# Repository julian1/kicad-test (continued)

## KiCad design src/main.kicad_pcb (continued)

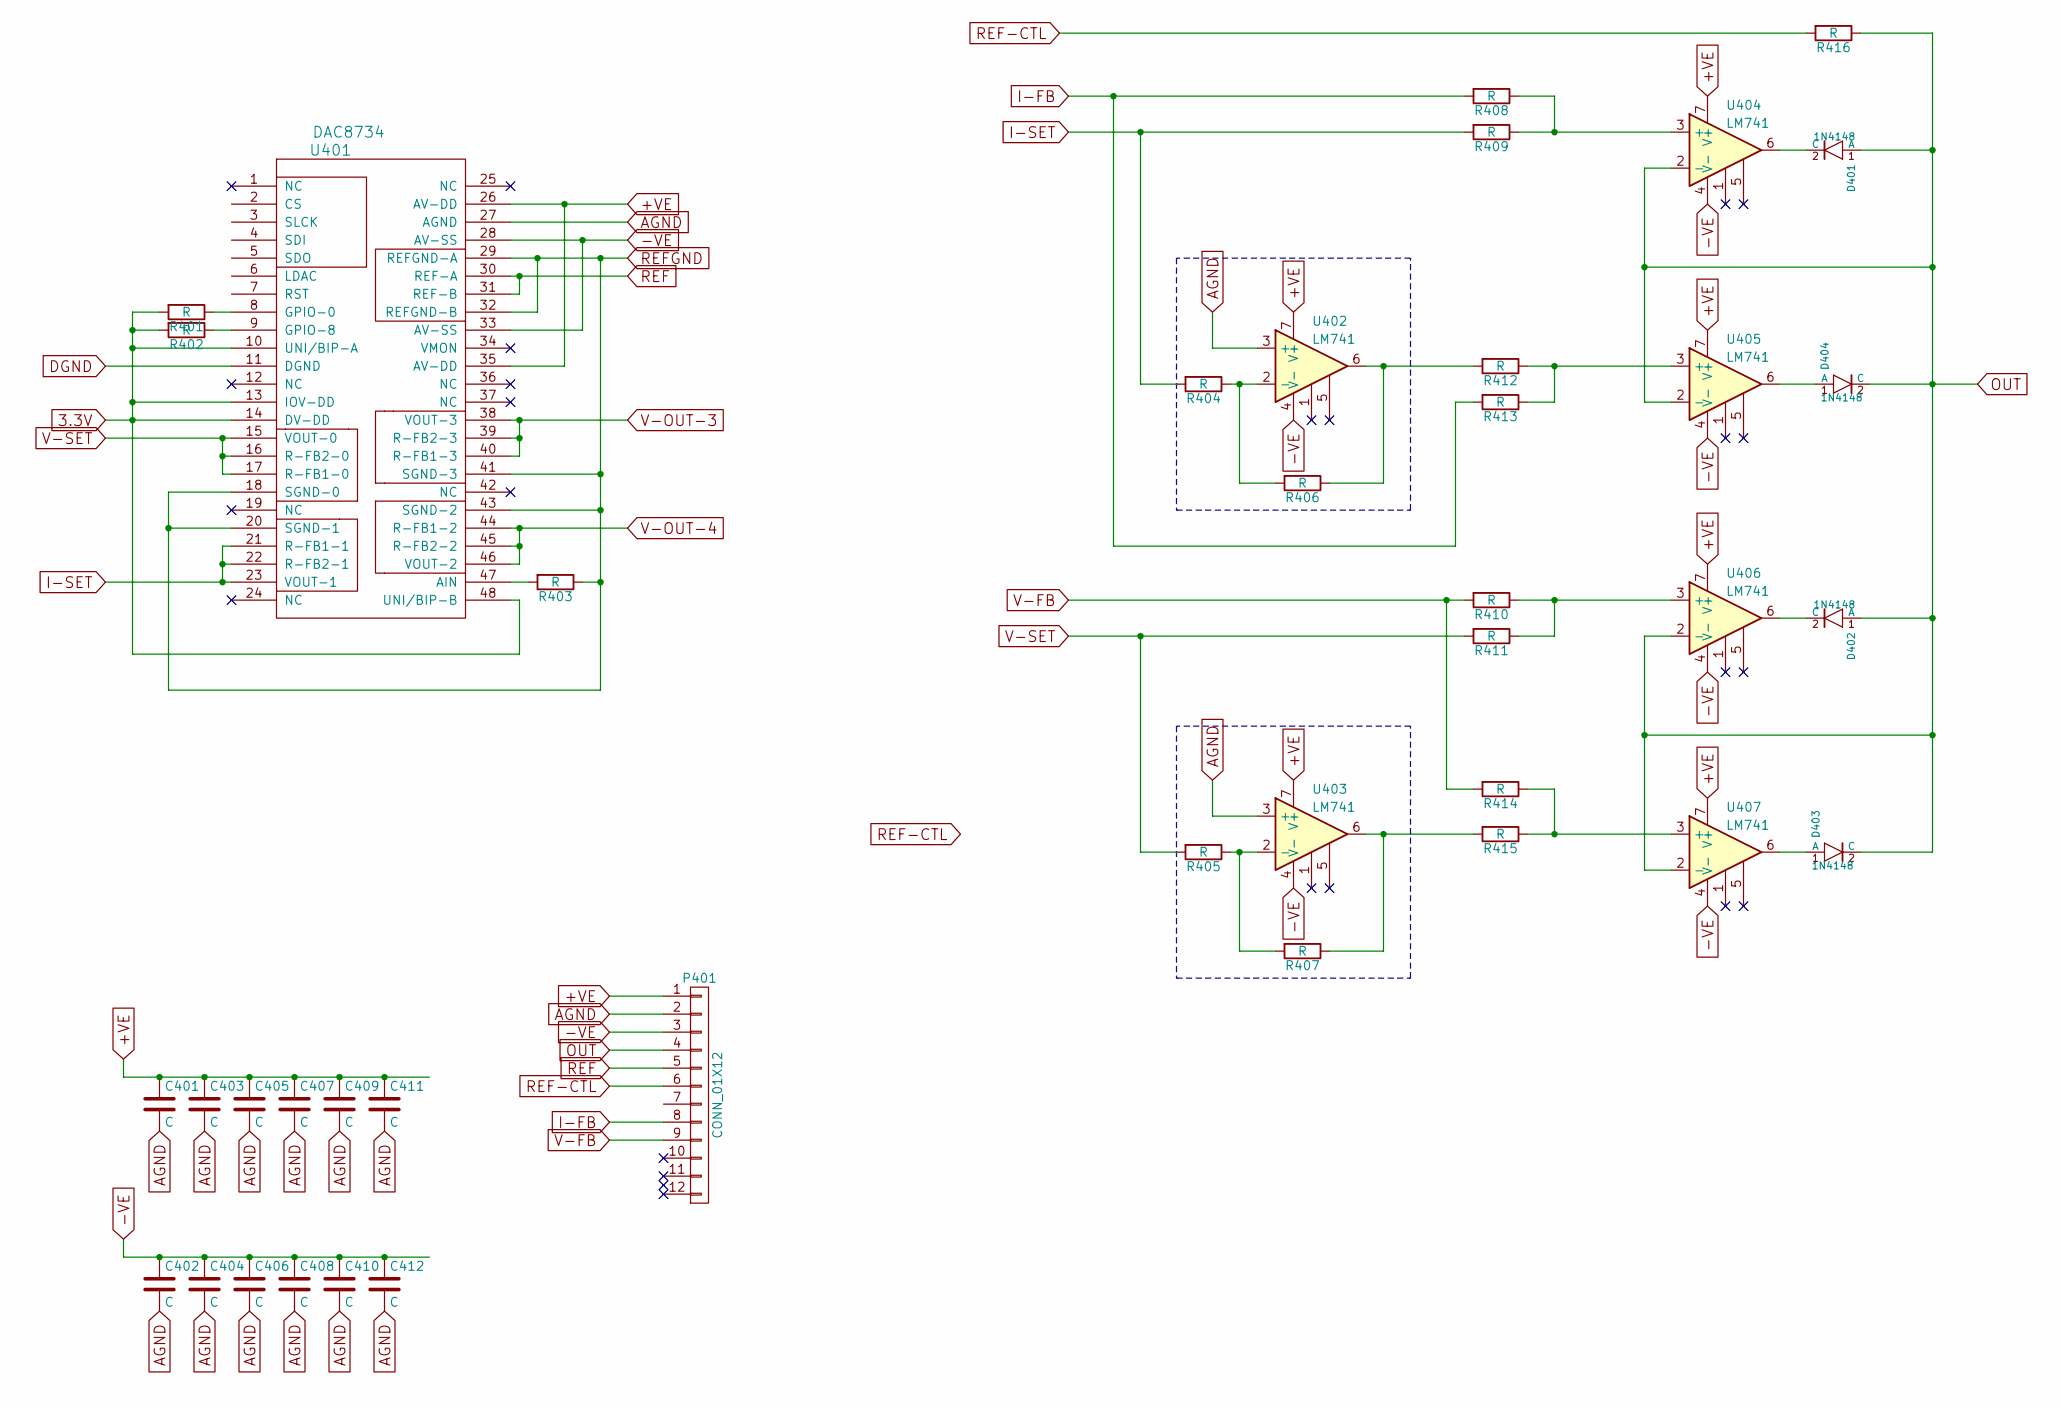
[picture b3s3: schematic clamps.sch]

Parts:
C401, C402, C403, C404, C405, C406, C407, C408, C409, C410, C411, C412: C; C_1206
D401, D402, D403, D404: 1N4148; MiniMELF_Standard
P401: CONN_01X12; Pin_Header_Straight_1x12
R401, R402, R403: R
R404, R405, R406, R407, R408, R409, R410, R411, R412, R413, R414, R415, R416: R; R_1206
U401: DAC8734
U402, U403, U404, U405, U406, U407: LM741; SOIC-8_3.9x4.9mm_Pitch1.27mm

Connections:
3.3V: R401.2, R402.2, U401.10 (UNI/BIP-A), U401.13 (IOV-DD), U401.14 (DV-DD), U401.48 (UNI/BIP-B); also elsewhere on the board
+VE: C401.1, C403.1, C405.1, C407.1, C409.1, C411.1, P401.1, U401.26 (AV-DD), U401.35 (AV-DD), U402.7 (V+), U403.7 (V+), U404.7 (V+), U405.7 (V+), U406.7 (V+), U407.7 (V+); also elsewhere on the board
-VE: C402.1, C404.1, C406.1, C408.1, C410.1, C412.1, P401.3, U401.28 (AV-SS), U401.33 (AV-SS), U402.4 (V-), U403.4 (V-), U404.4 (V-), U405.4 (V-), U406.4 (V-), U407.4 (V-); also elsewhere on the board
I-FB: P401.8, R408.2, R413.2
I-SET: R404.2, R409.2, U401.21 (R-FB1-1), U401.22 (R-FB2-1), U401.23 (VOUT-1)
unnamed: D401.2 (C), U404.6
unnamed: D402.2 (C), U406.6
unnamed: D403.1 (A), U407.6
unnamed: D404.1 (A), U405.6
unnamed: R401.1, U401.8 (GPIO-0)
unnamed: R402.1, U401.9 (GPIO-8)
unnamed: R403.2, U401.47 (AIN)
unnamed: R404.1, R406.2, U402.2 (-)
unnamed: R405.1, R407.2, U403.2 (-)
unnamed: R406.1, R412.2, U402.6
unnamed: R407.1, R415.2, U403.6
unnamed: R408.1, R409.1, U404.3 (+)
unnamed: R410.1, R411.1, U406.3 (+)
unnamed: R412.1, R413.1, U405.3 (+)
unnamed: R414.1, R415.1, U407.3 (+)
OUT: D401.1 (A), D402.1 (A), D403.2 (C), D404.2 (C), P401.4, R416.1, U404.2 (-), U405.2 (-), U406.2 (-), U407.2 (-)
REF: P401.5, U401.30 (REF-A), U401.31 (REF-B); also elsewhere on the board
REF-CTL: P401.6, R416.2
REFGND: R403.1, U401.18 (SGND-0), U401.20 (SGND-1), U401.29 (REFGND-A), U401.32 (REFGND-B), U401.41 (SGND-3), U401.43 (SGND-2)
V-FB: P401.9, R410.2, R414.2
V-OUT-3: U401.38 (VOUT-3), U401.39 (R-FB2-3), U401.40 (R-FB1-3)
V-OUT-4: U401.44 (R-FB1-2), U401.45 (R-FB2-2), U401.46 (VOUT-2)
V-SET: R405.2, R411.2, U401.15 (VOUT-0), U401.16 (R-FB2-0), U401.17 (R-FB1-0)

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
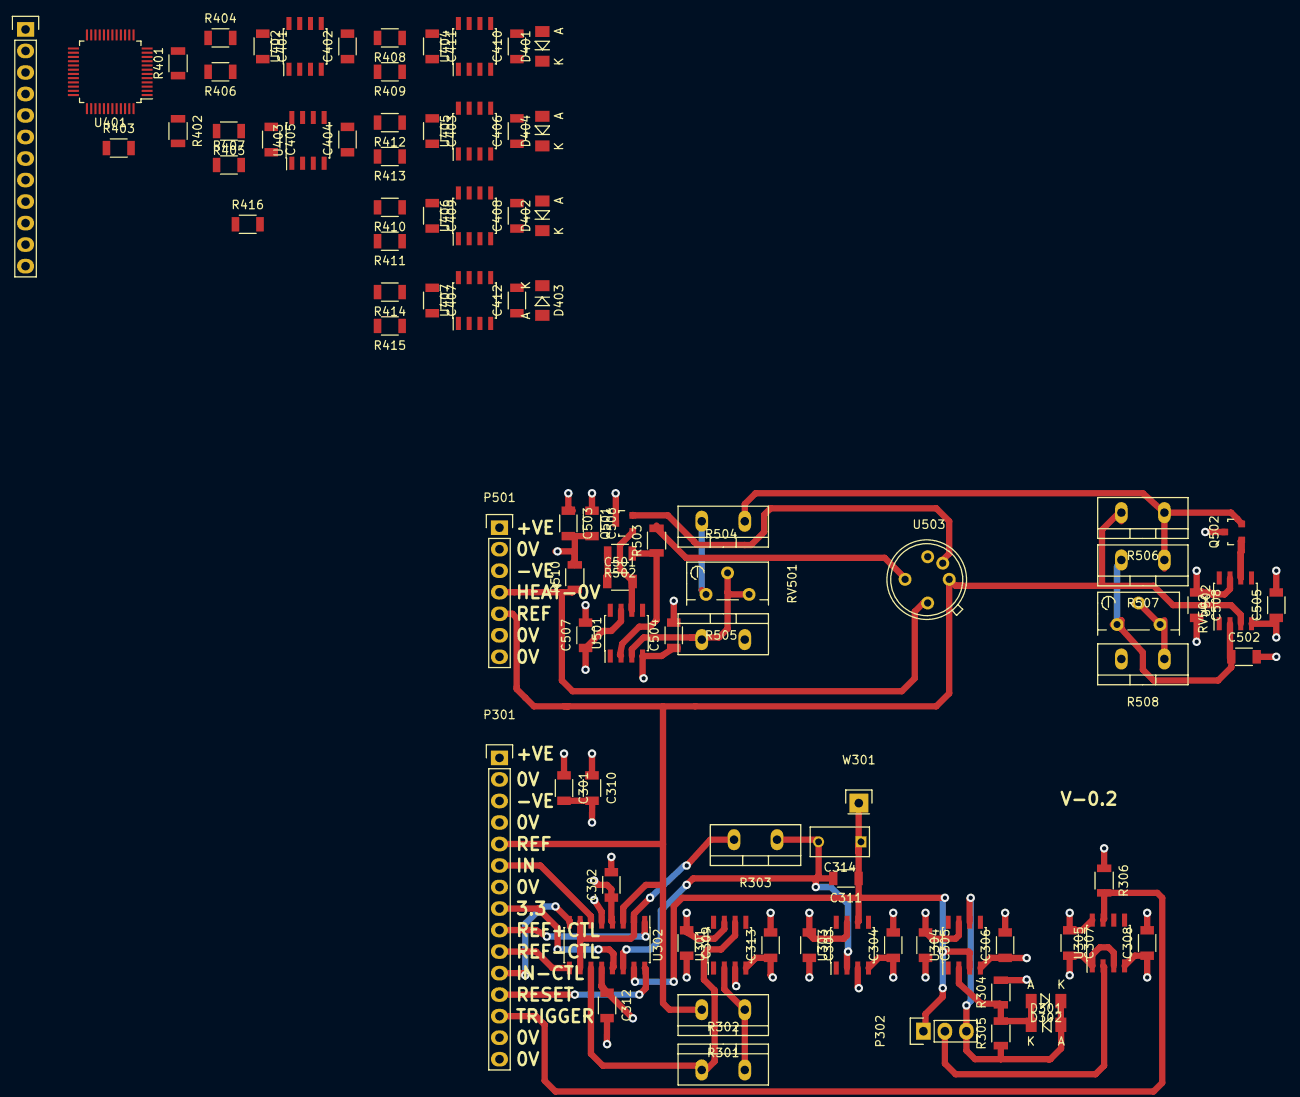
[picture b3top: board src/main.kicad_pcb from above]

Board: 4 copper layers, 94 parts (0 on the bottom side), 55 nets.

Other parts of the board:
R303: R; Resistor_TO-220_Vertical
U302: DG444; SOIC-16_3.9x9.9mm_Pitch1.27mm
U303: LM741; SOIC-8_3.9x4.9mm_Pitch1.27mm

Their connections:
3.3V: U302.13; also elsewhere on the board
+VE: U302.12, U303.7; also elsewhere on the board
-VE: U302.4, U303.4; also elsewhere on the board
IN: U302.6; also elsewhere on the board
IN_CTL: U302.8; also elsewhere on the board
unnamed 8: U302.15, U303.6; also elsewhere on the board
unnamed 9: R303.1, U302.14, U303.2; also elsewhere on the board
unnamed 24: U302.11; also elsewhere on the board
unnamed: R303.2, U302.2, U302.7, U302.10
REF: U302.3; also elsewhere on the board
REF_PLUS_CTL: U302.1; also elsewhere on the board
REF_SUB_CTL: U302.9; also elsewhere on the board
RESET: U302.16; also elsewhere on the board

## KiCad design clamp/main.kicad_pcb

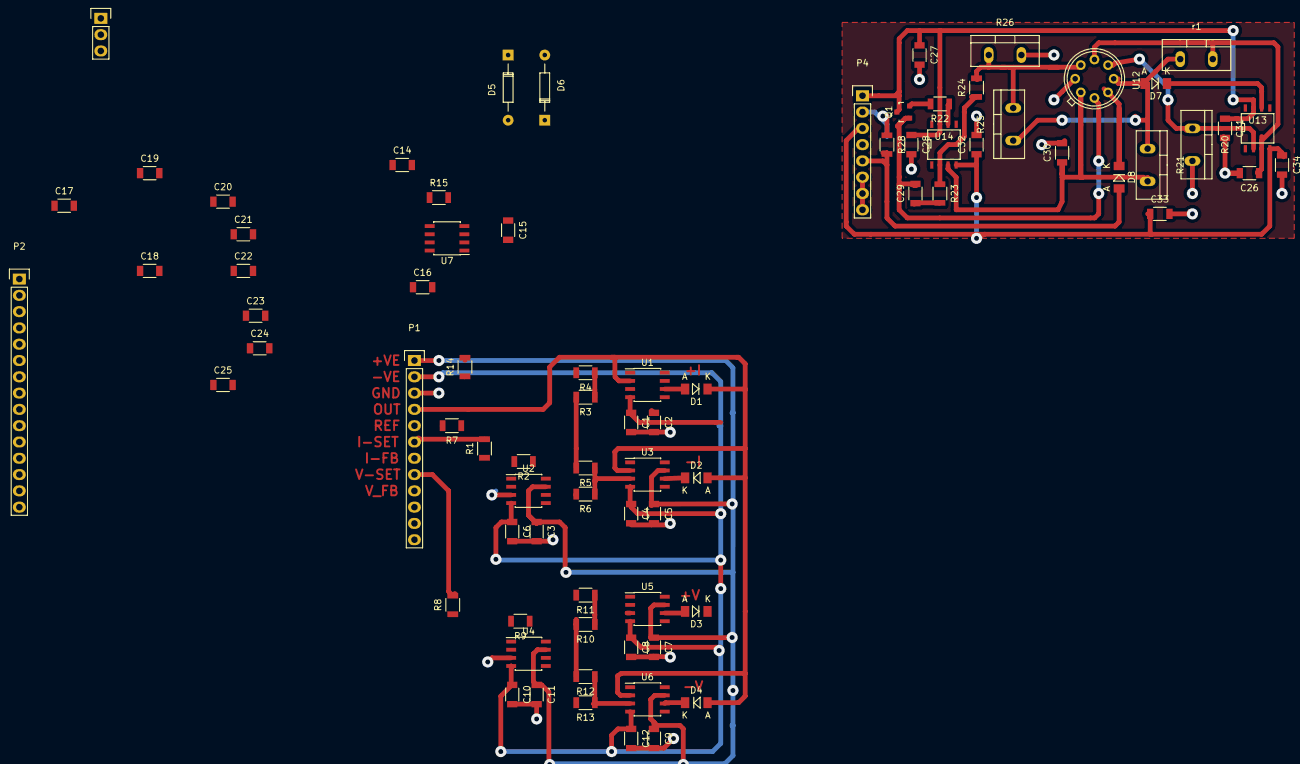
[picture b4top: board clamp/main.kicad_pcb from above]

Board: 2 copper layers, 80 parts (0 on the bottom side), 37 nets.

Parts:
C1, C2, C3, C4, C5, C6, C7, C8, C9, C10, C11, C12, C14, C15, C16, C17, C18, C19, C20, C21, C22, C23, C24, C25: C; C_1206
C26: 22nF; C_1206
C27, C33: 10uF; C_1206
C28, C29, C30, C31, C32, C34: 0.1uF; C_1206
D1, D2, D3, D4, D7, D8: 1N4148; MiniMELF_Standard
D5, D6: 1N4148; Diode_DO-35_SOD27_Horizontal_RM10
P1: CONN_01X12; Pin_Header_Straight_1x12
P2: CONN_01X15; Pin_Header_Straight_1x15
P3: CONN_01X03; Pin_Header_Straight_1x03
P4: CONN_01X08; Pin_Header_Straight_1x08
Q1: 2N3904; SOT-23
R1, R2, R3, R4, R5, R6, R7, R8, R9, R10, R11, R12, R13, R14, R15: R; R_1206
R20: 120; Resistor_TO-220_Vertical
R21: 70k; Resistor_TO-220_Vertical
R22: 1k; R_1206
R23: 1M; R_1206
R24: 10k; R_1206
R25: 12k; Resistor_TO-220_Vertical
R26: 1k; Resistor_TO-220_Vertical
R28: 0; R_1206
U1, U2, U3, U4, U5, U6, U7: LM741; SOIC-8_3.9x4.9mm_Pitch1.27mm
U12: LTZ1000; TO-5_Housing_8Pin
U13, U14: LM741; SOIC-8-N
r1: 70k; Resistor_TO-220_Vertical

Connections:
+VE: C1.1, C3.1, C5.1, C7.1, C9.1, C11.1, C14.1, C16.1, C18.1, C20.1, C22.1, C24.1, C27.1, C28.1, C31.1, P1.1, P2.1, P4.1, Q1.3, U1.7, U2.7, U3.7, U4.7, U5.7, U6.7, U7.7, U13.7, U14.7
-VE: C2.1, C4.1, C6.1, C8.1, C10.1, C12.1, C15.1, C17.1, C19.1, C21.1, C23.1, C25.1, C32.1, C33.1, C34.1, P1.2, P2.3, P4.3, U1.4, U2.4, U3.4, U4.4, U5.4, U6.4, U7.4, U13.4, U14.4
GND: C1.2, C2.2, C3.2, C4.2, C5.2, C6.2, C7.2, C8.2, C9.2, C10.2, C11.2, C12.2, C14.2, C15.2, C16.2, C17.2, C18.2, C19.2, C20.2, C21.2, C22.2, C23.2, C24.2, C25.2, C26.2, C27.2, C28.2, C30.2, C31.2, C32.2, C33.2, C34.2, P1.3, P2.2, P2.4, P2.7, P2.14, P2.15, P4.2, P4.6, P4.7, P4.8, R20.2, R26.2, R28.1, U1.3, U2.3, U7.3, U12.7
GND-H: D8.2, P4.5, R28.2
I-FB: P1.7, R5.2, R10.2
I-SET: P1.6, R1.2, R6.2
unnamed: C26.1, U12.5, U13.3, r1.2
unnamed: C29.1, R23.2
unnamed: C29.2, Q1.1, U12.1
unnamed: C30.1, R21.2, U12.8, U14.3
unnamed: D1.2, U3.6
unnamed: D2.2, U5.6
unnamed: D3.1, U6.6
unnamed: D4.1, U4.6
unnamed: D5.1, D6.2
unnamed: D5.2, D6.1, P3.3
unnamed: D7.1, U13.6
unnamed: D8.1, U12.2
unnamed: Q1.2, R22.2
unnamed: R1.1, R3.2, U1.2
unnamed: R2.1, R4.2, U2.2
unnamed: R3.1, R9.2, U1.6
unnamed: R5.1, R6.1, U3.3
unnamed: R7.1, R8.1, U5.3
unnamed: R9.1, R10.1, U4.3
unnamed: R11.1, R12.1, U6.3
unnamed: R4.1, R12.2, U2.6
unnamed: R14.1, R15.2, U7.2
unnamed: R15.1, U7.6
unnamed: R20.1, U12.4, U13.2
unnamed: R22.1, U14.6
unnamed: R23.1, R24.1, U14.2
unnamed: R24.2, R25.2, R26.1, U12.6
OUT: D1.1, D2.1, D3.2, D4.2, P1.4, R13.1, U3.2, U4.2, U5.2, U6.2
REF: D7.2, P1.5, P2.5, P4.4, R13.2, R14.2, R21.1, R25.1, U12.3, r1.1
V-FB: P1.9, R7.2, R11.2
V-SET: P1.8, R2.2, R8.2

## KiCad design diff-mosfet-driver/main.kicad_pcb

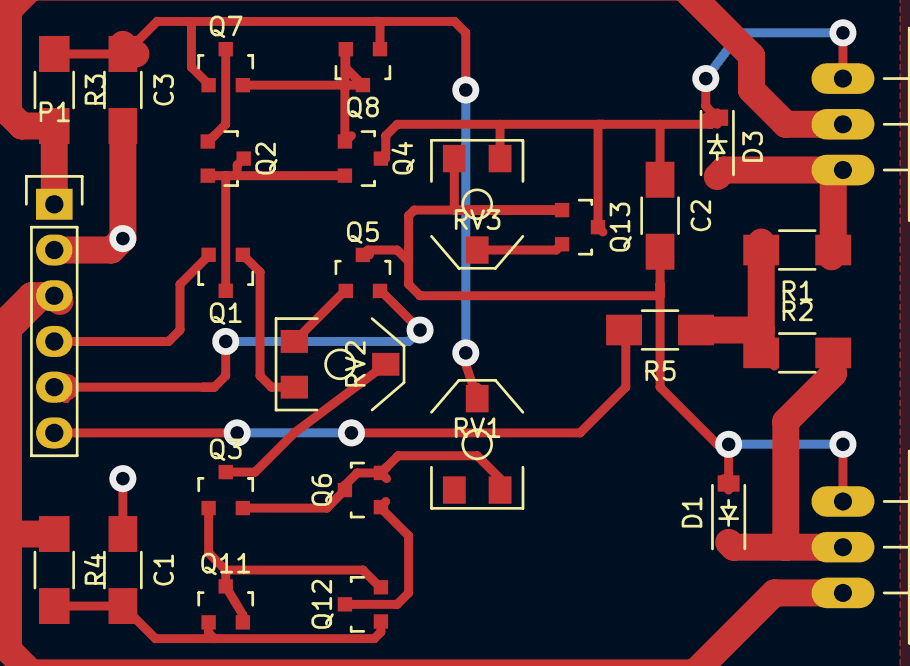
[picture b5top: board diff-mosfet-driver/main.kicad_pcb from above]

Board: 2 copper layers, 27 parts (0 on the bottom side), 23 nets.

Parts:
C1, C2, C3: C; C_1206_HandSoldering
D1, D3: ZENER; SOD-123
P1: CONN_01X06; Pin_Header_Straight_1x06
Q1, Q5: MOS_N; SOT-23
Q2, Q4, Q7, Q8: 2N3906; SOT-23
Q3, Q6, Q11, Q12, Q13: 2N3904; SOT-23
Q9: IRF540N; TO-220_Neutral123_Horizontal_LargePads
Q10: IRF9540N; TO-220_Neutral123_Horizontal_LargePads
R1, R2, R3, R4, R5: R; R_1206_HandSoldering
RV1, RV2, RV3: POT; POT_SMD

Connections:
+VE: P1.1, Q9.2, R3.2
-VE: P1.3, Q10.3, R4.1
unnamed: C1.1, C3.2, P1.2
unnamed: C1.2, Q11.1, Q12.1, R4.2
unnamed: C2.1, D3.1, Q4.3, Q9.1, Q13.3, RV3.1
unnamed: C2.2, D1.2, Q5.3, Q10.1, Q13.1, RV3.3
unnamed: C3.1, Q7.1, Q8.1, R3.1, RV1.2
unnamed: D1.1, Q10.2, R2.2
unnamed: D3.2, Q9.3, R1.1
unnamed: P1.4, Q1.2
unnamed: P1.5, Q5.2
unnamed: P1.6, R5.2
unnamed: Q1.1, RV2.3
unnamed: Q1.3, Q2.2, Q2.3, Q4.2
unnamed: Q2.1, Q7.3
unnamed: Q3.2, Q6.2, Q6.3, RV1.3
unnamed: Q3.3, RV2.2
unnamed: Q4.1, Q7.2, Q8.2, Q8.3
unnamed: Q5.1, RV2.1
unnamed: Q3.1, Q11.2, Q11.3, Q12.2
unnamed: Q6.1, Q12.3
unnamed: Q13.2, RV3.2
unnamed: R1.2, R2.1, R5.1

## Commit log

2016-10-20 rebased to root
2016-10-20 add clamp gerber
2016-10-21 change to non hand-soldered 1206
2016-10-22 add 0R jumpers
2016-10-22 add 0R values
2016-10-22 increased vias
2016-10-22 added heirarchical sheet
2016-10-22 tidy
2016-12-26 add ADC
2016-12-26 move clamps
2016-12-26 annotate
2016-12-26 move items
2016-12-26 gitignore
2016-12-27 add trigger pullup
2016-12-28 add clamp ref
2016-12-28 add ltz1000
2016-12-28 initial ref
2016-12-28 add ref decoupling
2016-12-28 basic layout
2016-12-28 new footprint to-5
2016-12-29 pcb for first bit
2016-12-29 add heater feedback to ref
2016-12-29 looks ok
2016-12-30 add resistor divider in place of pot
2016-12-30 fix bodge
2016-12-30 tie diode out to gnd not -ve
2016-12-31 remove nc
2017-01-04 add extra caps, and separate heater gnd return
2017-01-04 remove trimpot add extra resitor
2017-01-17 move diode closer
2017-01-20 add 2dw232
2017-01-20 4 layer
2017-01-20 looks good
2017-01-20 just the dw232
2017-01-20 remove old
2017-01-20 remove pin header vias
2017-01-21 complete
2017-01-21 shorter underneath traces
2017-01-21 improve
2017-01-21 move right
2017-01-22 turn off attributes
2017-01-30 change schematic from 0V to AGND
2017-01-30 fix and annotate clamps
2017-01-30 change pcb from 0V to AGND
2017-01-30 initial clamps pcb
2017-02-14 update before refactor
2017-02-14 move main to project-01
2017-02-14 update zip file creation
2017-02-14 refactor into sheets and projects
2017-02-14 add dw232
2017-02-14 Revert "update"
    This reverts commit faaf303909b951c94a4a4b316b335292b67975f1.
2017-02-14 remove old stuff for reference
2017-02-14 clean up pcb
2017-02-14 change trimmers to fixed resistors
2017-02-14 annotate component values
2017-02-14 ok pcb saved
2017-02-14 after autoroute, but before planes
2017-02-15 remove old gerbers
2017-02-15 move zip.sh
2017-02-15 add 2dw232 gerbers
2017-02-15 add autorouter files
2017-02-15 reposition silkscreen lttering
2017-02-15 fix front and back silk
2017-02-15 fix fills, text
2017-02-15 copyright
2017-02-15 regenerate gerbers
2017-02-15 make masks not filled
2017-02-15 add edge cuts
2017-02-17 update todo
2017-02-18 change clamps to use quad op-amp
2017-02-18 fix dg444 and dac power inputs
2017-02-18 remove 2dw232 from smu
2017-02-18 fixed design rules checks
2017-02-18 add analog switch
2017-02-18 add net-ties where needed
2017-02-19 pulled out the connectors to the top sheet
2017-02-19 generate net and parts
2017-02-19 add nettie library etc
2017-02-19 change resistors to all 1206
2017-02-19 do edges again
2017-02-19 ok somewhat laid out
2017-02-19 ok routed
2017-02-22 add lt1021, remove net-tie
2017-02-22 add power
2017-02-22 renaming pins
2017-02-26 v0.2 2dw232
2017-02-26 update components
2017-02-26 adjust positions
2017-02-26 ok, routed and reasonable
2017-02-26 reset
2017-02-26 before ses import
2017-02-27 better
2017-02-27 fill in gnd
2017-02-27 gerber
2017-02-27 fix copyright
2017-03-08 2dw232 board revision 2
2017-03-08 add initial filter
2017-03-12 add output section
2017-03-12 split pin-headers into analog and digital
2017-03-13 add schematic for relay
2017-03-13 initial feedback
2017-03-23 fix schematic v0.3
2020-09-08 edit libraries
2020-09-08 fuck
2020-09-08 fuck2
2020-09-08 checkin believed format for libraries
